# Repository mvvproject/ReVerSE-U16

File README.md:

# ReVerSE-U16
Development Kit

Плата ReVerSE-U16 ориентированна на создание SoC систем на микросхеме программируемой логики ПЛИС. Отлично подходит для домашнего обучения и позволяет полностью воссоздать множество ретро-компьютеров.
Для программирования используются программаторы и отладочные среды, позволяющие задать желаемую структуру цифрового устройства в виде принципиальной электрической схемы или программы на специальных языках описания аппаратуры: Verilog, VHDL, AHDL и др. В конфигурации ПЛИС реализуются почти все компоненты компьютера. Вне ПЛИС находятся только оперативная память, аппаратные интерфейсы для подключения клавиатуры, мыши, монитора, и других устройств.

#### Спецификация:
- FPGA Cyclone IV EP4CE22E22C8N (supports Cyclone III EP3C5/10/16/25, Cyclone IV EP4CE6/10/15/22)
- SDRAM 16MB x 16 bit (supports 4/16/32MB x 16 bit)
- SPI FLASH 64Mb (supports 64/16/1Mb)
- RTC DS1338Z + CR2032
- HDMI for sound and video (DVI or HDMI Male to VGA HD-15 15Pin Male Adapter Cable Cord)
- 10/100 Base-T Ethernet interface controller ENC424J600 with integrated MAC & PHY
- Dual USB 2.0 Host / Slave controller VNC2 (2 x ports)
- micro SD
- JTAG
- GPIO (uBUS)
- Power +5В 1A
- PCB Size 70 х 56 mm

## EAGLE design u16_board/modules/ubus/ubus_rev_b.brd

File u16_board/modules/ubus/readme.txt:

ReVerSE-U16 Adapter uBUS

09.06.2015	Rev.A Первая версия
16.09.2015	Rev.B Добавлены светодиоды LED1-8
05.10.2015	Rev.C Добавлена поддержка слотов расширения ZX-Bus, Nemo-Bus, NES, MSX-Bus

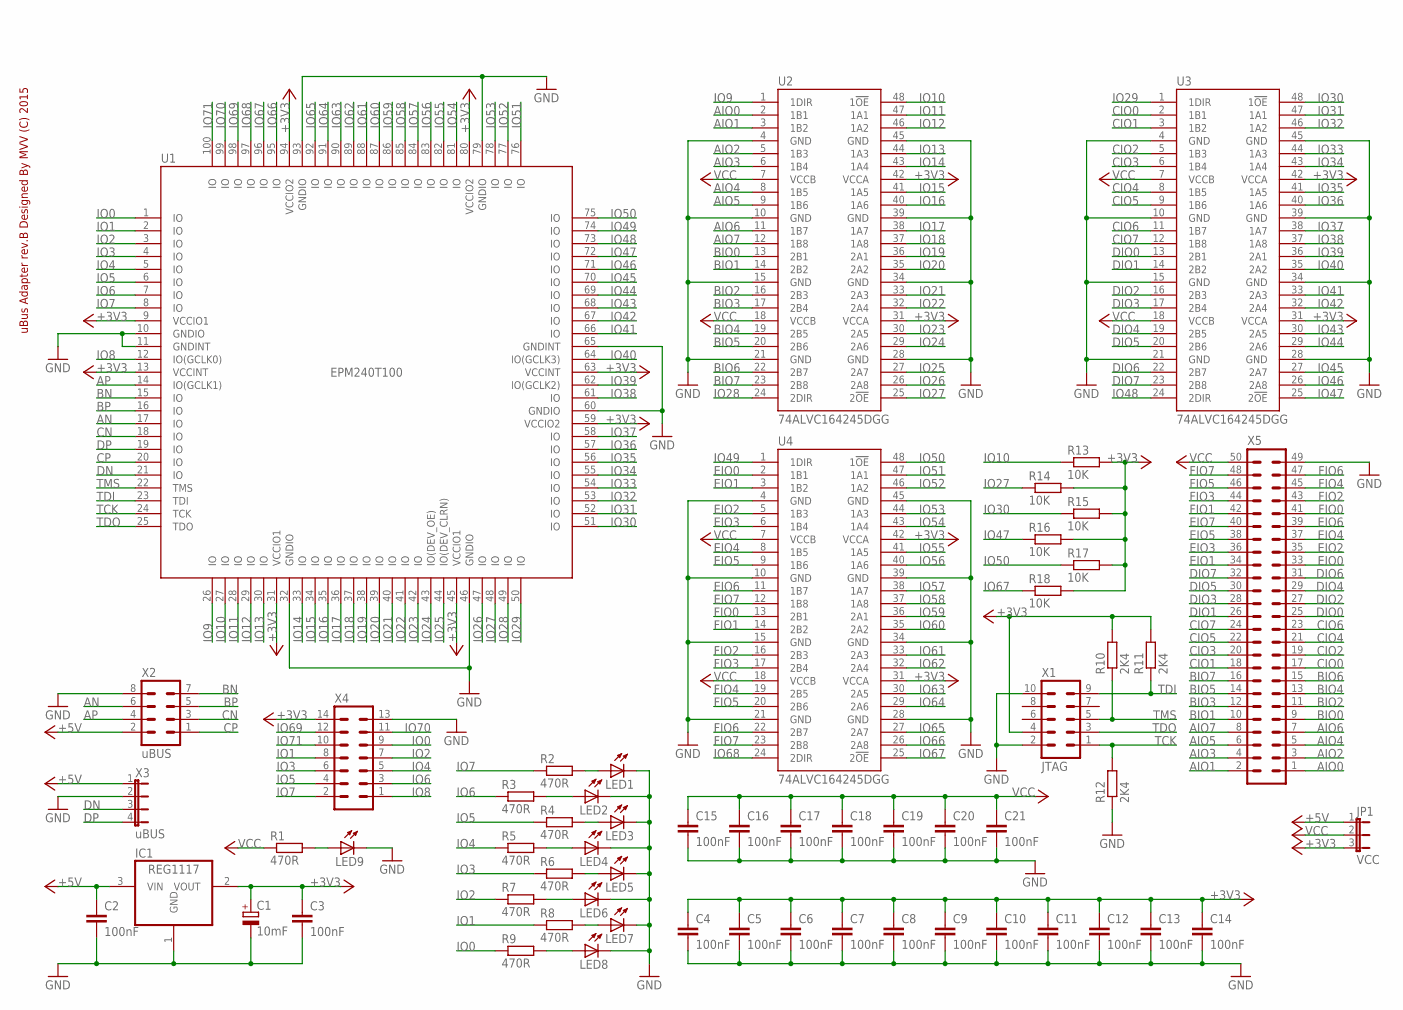
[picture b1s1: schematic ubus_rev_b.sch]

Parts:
C1: 10mF; CT6032
C2, C3, C4, C5, C6, C7, C8, C9, C10, C11, C12, C13, C14, C15, C16, C17, C18, C19, C20, C21: 100nF; C0805
IC1: REG1117; SOT223
JP1: VCC; JP2
LED1, LED2, LED3, LED4, LED5, LED6, LED7, LED8, LED9: LEDCHIPLED_0805; CHIPLED_0805
R1, R2, R3, R4, R5, R6, R7, R8, R9: 470R; R0805
R10, R11, R12: 2K4; R0805
R13, R14, R15, R16, R17, R18: 10K; R0805
U1: EPM240T100; TQFP100
U2, U3, U4: 74ALVC164245DGG; TSSOP48DGG
X1: JTAG; ML10
X2: uBUS; MA04-2
X3: uBUS; JP4
X4: ML14
X5: ML50

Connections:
+3V3: C1.+, C3.1, C4.1, C5.1, C6.1, C7.1, C8.1, C9.1, C10.1, C11.1, C12.1, C13.1, C14.1, IC1.2 (VOUT), JP1.3, R10.2, R11.2, R13.2, R14.2, R15.2, R16.2, R17.2, R18.2, U1.9 (VCCIO1), U1.13 (VCCINT), U1.31 (VCCIO1), U1.45 (VCCIO1), U1.59 (VCCIO2), U1.63 (VCCINT), U1.80 (VCCIO2), U1.94 (VCCIO2), U2.31 (VCCA), U2.42 (VCCA), U3.31 (VCCA), U3.42 (VCCA), U4.31 (VCCA), U4.42 (VCCA), X1.4, X4.14
+5V: C2.1, IC1.3 (VIN), JP1.1, X2.2, X3.1
AIO0: U2.2 (1B1), X5.1
AIO1: U2.3 (1B2), X5.2
AIO2: U2.5 (1B3), X5.3
AIO3: U2.6 (1B4), X5.4
AIO4: U2.8 (1B5), X5.5
AIO5: U2.9 (1B6), X5.6
AIO6: U2.11 (1B7), X5.7
AIO7: U2.12 (1B8), X5.8
AN: U1.17 (IO), X2.6
AP: U1.14 (IO(GCLK1)), X2.4
BIO0: U2.13 (2B1), X5.9
BIO1: U2.14 (2B2), X5.10
BIO2: U2.16 (2B3), X5.11
BIO3: U2.17 (2B4), X5.12
BIO4: U2.19 (2B5), X5.13
BIO5: U2.20 (2B6), X5.14
BIO6: U2.22 (2B7), X5.15
BIO7: U2.23 (2B8), X5.16
BN: U1.15 (IO), X2.7
BP: U1.16 (IO), X2.5
CIO0: U3.2 (1B1), X5.17
CIO1: U3.3 (1B2), X5.18
CIO2: U3.5 (1B3), X5.19
CIO3: U3.6 (1B4), X5.20
CIO4: U3.8 (1B5), X5.21
CIO5: U3.9 (1B6), X5.22
CIO6: U3.11 (1B7), X5.23
CIO7: U3.12 (1B8), X5.24
CN: U1.18 (IO), X2.3
CP: U1.20 (IO), X2.1
DIO0: U3.13 (2B1), X5.25
DIO1: U3.14 (2B2), X5.26
DIO2: U3.16 (2B3), X5.27
DIO3: U3.17 (2B4), X5.28
DIO4: U3.19 (2B5), X5.29
DIO5: U3.20 (2B6), X5.30
DIO6: U3.22 (2B7), X5.31
DIO7: U3.23 (2B8), X5.32
DN: U1.21 (IO), X3.3
DP: U1.19 (IO), X3.4
EIO0: U4.2 (1B1), X5.33
EIO1: U4.3 (1B2), X5.34
EIO2: U4.5 (1B3), X5.35
EIO3: U4.6 (1B4), X5.36
EIO4: U4.8 (1B5), X5.37
EIO5: U4.9 (1B6), X5.38
EIO6: U4.11 (1B7), X5.39
EIO7: U4.12 (1B8), X5.40
FIO0: U4.13 (2B1), X5.41
FIO1: U4.14 (2B2), X5.42
FIO2: U4.16 (2B3), X5.43
FIO3: U4.17 (2B4), X5.44
FIO4: U4.19 (2B5), X5.45
FIO5: U4.20 (2B6), X5.46
FIO6: U4.22 (2B7), X5.47
FIO7: U4.23 (2B8), X5.48
GND: C1.-, C2.2, C3.2, C4.2, C5.2, C6.2, C7.2, C8.2, C9.2, C10.2, C11.2, C12.2, C13.2, C14.2, C15.2, C16.2, C17.2, C18.2, C19.2, C20.2, C21.2, IC1.1 (GND), LED1.C, LED2.C, LED3.C, LED4.C, LED5.C, LED6.C, LED7.C, LED8.C, LED9.C, R12.1, U1.10 (GNDIO), U1.11 (GNDINT), U1.32 (GNDIO), U1.46 (GNDIO), U1.60 (GNDIO), U1.65 (GNDINT), U1.79 (GNDIO), U1.93 (GNDIO), U2.4 (GND), U2.10 (GND), U2.15 (GND), U2.21 (GND), U2.28 (GND), U2.34 (GND), U2.39 (GND), U2.45 (GND), U3.4 (GND), U3.10 (GND), U3.15 (GND), U3.21 (GND), U3.28 (GND), U3.34 (GND), U3.39 (GND), U3.45 (GND), U4.4 (GND), U4.10 (GND), U4.15 (GND), U4.21 (GND), U4.28 (GND), U4.34 (GND), U4.39 (GND), U4.45 (GND), X1.2, X1.10, X2.8, X3.2, X4.13, X5.49
IO0: R9.1, U1.1 (IO), X4.9
IO1: R8.1, U1.2 (IO), X4.8
IO2: R7.1, U1.3 (IO), X4.7
IO3: R6.1, U1.4 (IO), X4.6
IO4: R5.1, U1.5 (IO), X4.5
IO5: R4.1, U1.6 (IO), X4.4
IO6: R3.1, U1.7 (IO), X4.3
IO7: R2.1, U1.8 (IO), X4.2
IO8: U1.12 (IO(GCLK0)), X4.1
IO9: U1.26 (IO), U2.1 (1DIR)
IO10: R13.1, U1.27 (IO), U2.48 (1!OE)
IO11: U1.28 (IO), U2.47 (1A1)
IO12: U1.29 (IO), U2.46 (1A2)
IO13: U1.30 (IO), U2.44 (1A3)
IO14: U1.33 (IO), U2.43 (1A4)
IO15: U1.34 (IO), U2.41 (1A5)
IO16: U1.35 (IO), U2.40 (1A6)
IO17: U1.36 (IO), U2.38 (1A7)
IO18: U1.37 (IO), U2.37 (1A8)
IO19: U1.38 (IO), U2.36 (2A1)
IO20: U1.39 (IO), U2.35 (2A2)
IO21: U1.40 (IO), U2.33 (2A3)
IO22: U1.41 (IO), U2.32 (2A4)
IO23: U1.42 (IO), U2.30 (2A5)
IO24: U1.43 (IO(DEV_OE)), U2.29 (2A6)
IO25: U1.44 (IO(DEV_CLRN)), U2.27 (2A7)
IO26: U1.47 (IO), U2.26 (2A8)
IO27: R14.1, U1.48 (IO), U2.25 (2!OE)
IO28: U1.49 (IO), U2.24 (2DIR)
IO29: U1.50 (IO), U3.1 (1DIR)
IO30: R15.1, U1.51 (IO), U3.48 (1!OE)
IO31: U1.52 (IO), U3.47 (1A1)
IO32: U1.53 (IO), U3.46 (1A2)
IO33: U1.54 (IO), U3.44 (1A3)
IO34: U1.55 (IO), U3.43 (1A4)
IO35: U1.56 (IO), U3.41 (1A5)
IO36: U1.57 (IO), U3.40 (1A6)
IO37: U1.58 (IO), U3.38 (1A7)
IO38: U1.61 (IO), U3.37 (1A8)
IO39: U1.62 (IO(GCLK2)), U3.36 (2A1)
IO40: U1.64 (IO(GCLK3)), U3.35 (2A2)
IO41: U1.66 (IO), U3.33 (2A3)
IO42: U1.67 (IO), U3.32 (2A4)
IO43: U1.68 (IO), U3.30 (2A5)
IO44: U1.69 (IO), U3.29 (2A6)
IO45: U1.70 (IO), U3.27 (2A7)
IO46: U1.71 (IO), U3.26 (2A8)
IO47: R16.1, U1.72 (IO), U3.25 (2!OE)
IO48: U1.73 (IO), U3.24 (2DIR)
IO49: U1.74 (IO), U4.1 (1DIR)
IO50: R17.1, U1.75 (IO), U4.48 (1!OE)
IO51: U1.76 (IO), U4.47 (1A1)
IO52: U1.77 (IO), U4.46 (1A2)
IO53: U1.78 (IO), U4.44 (1A3)
IO54: U1.81 (IO), U4.43 (1A4)
IO55: U1.82 (IO), U4.41 (1A5)
IO56: U1.83 (IO), U4.40 (1A6)
IO57: U1.84 (IO), U4.38 (1A7)
IO58: U1.85 (IO), U4.37 (1A8)
IO59: U1.86 (IO), U4.36 (2A1)
IO60: U1.87 (IO), U4.35 (2A2)
IO61: U1.88 (IO), U4.33 (2A3)
IO62: U1.89 (IO), U4.32 (2A4)
IO63: U1.90 (IO), U4.30 (2A5)
IO64: U1.91 (IO), U4.29 (2A6)
IO65: U1.92 (IO), U4.27 (2A7)
IO66: U1.95 (IO), U4.26 (2A8)
IO67: R18.1, U1.96 (IO), U4.25 (2!OE)
IO68: U1.97 (IO), U4.24 (2DIR)
IO69: U1.98 (IO), X4.12
IO70: U1.99 (IO), X4.11
IO71: U1.100 (IO), X4.10
unnamed: LED1.A, R2.2
unnamed: LED2.A, R3.2
unnamed: LED3.A, R4.2
unnamed: LED4.A, R5.2
unnamed: LED5.A, R6.2
unnamed: LED6.A, R7.2
unnamed: LED7.A, R8.2
unnamed: LED8.A, R9.2
unnamed: LED9.A, R1.2
TCK: R12.2, U1.24 (TCK), X1.1
TDI: R11.1, U1.23 (TDI), X1.9
TDO: U1.25 (TDO), X1.3
TMS: R10.1, U1.22 (TMS), X1.5
VCC: C15.1, C16.1, C17.1, C18.1, C19.1, C20.1, C21.1, JP1.2, R1.1, U2.7 (VCCB), U2.18 (VCCB), U3.7 (VCCB), U3.18 (VCCB), U4.7 (VCCB), U4.18 (VCCB), X5.50

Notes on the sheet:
uBus Adapter rev.B Designed By MVV (C) 2015

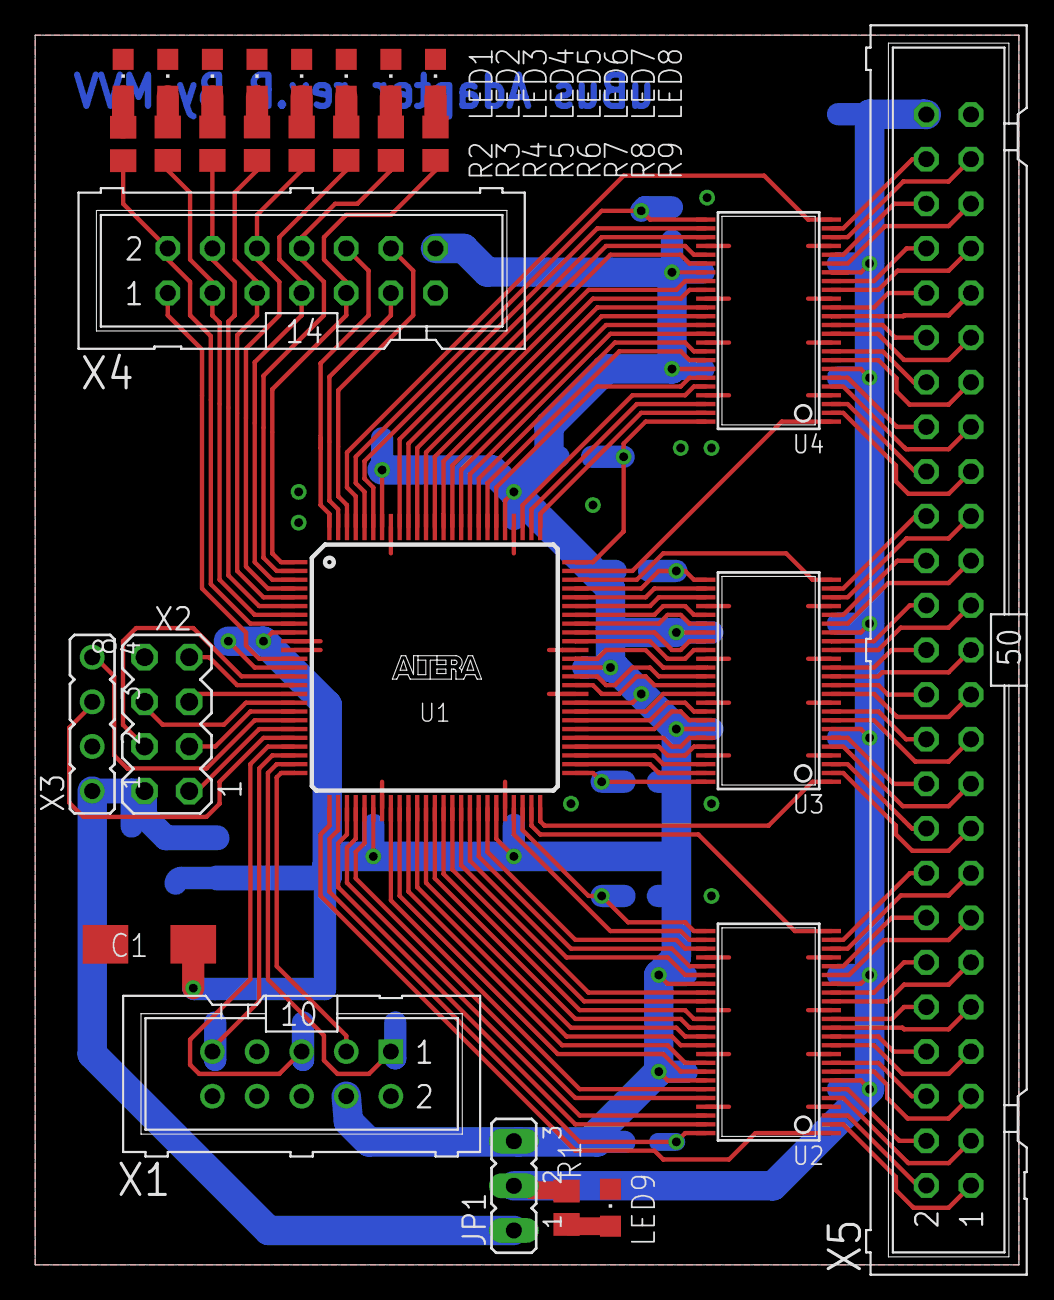
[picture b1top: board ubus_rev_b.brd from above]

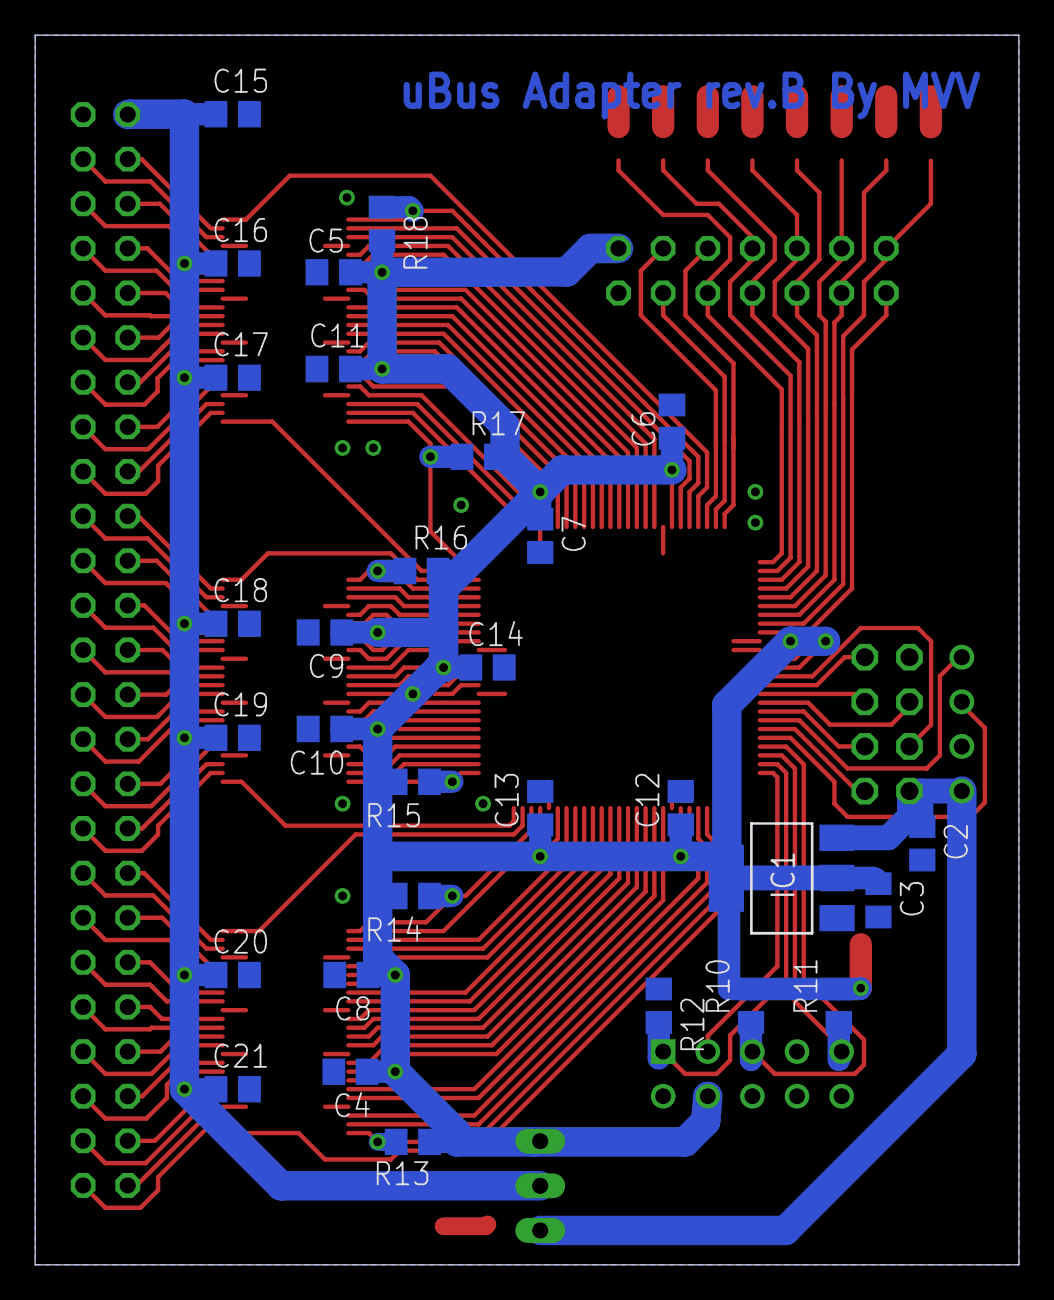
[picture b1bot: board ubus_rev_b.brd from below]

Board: 2 copper layers, 56.0 x 70.0 mm, 59 parts (30 on the bottom side), 145 nets.

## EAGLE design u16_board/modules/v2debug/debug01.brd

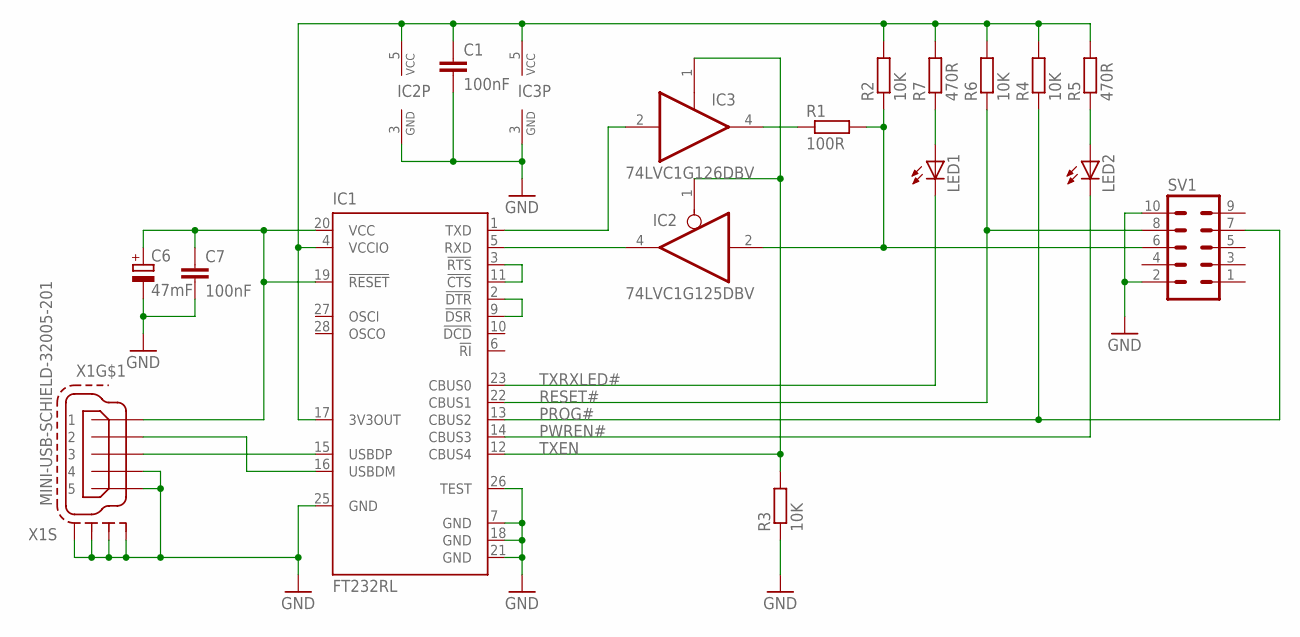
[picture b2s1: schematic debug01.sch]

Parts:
C1, C7: 100nF; C0603
C6: 47mF; CT3528
IC1: FT232RL; SSOP28
IC2: 74LVC1G125DBV; SOT23-5
IC3: 74LVC1G126DBV; SOT23-5
LED1, LED2: LEDCHIPLED_0805; CHIPLED_0805
R1: 100R; R0603
R2, R4, R6: 10K; R0603
R3: 10K; R1206
R5, R7: 470R; R0603
SV1: ML10
X1: MINI-USB-SCHIELD-32005-201; 32005-201

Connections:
+3V3: C1.1, IC1.4 (VCCIO), IC1.17 (3V3OUT), IC2.5 (VCC), IC3.5 (VCC), R2.2, R4.2, R5.2, R6.2, R7.2
+5V0: C6.+, C7.1, IC1.19 (!RESET), IC1.20 (VCC), X1.1
DBG: IC2.2 (I), R1.2, R2.1, SV1.6
DM: IC1.16 (USBDM), X1.2
DP: IC1.15 (USBDP), X1.3
GND: C1.2, C6.-, C7.2, IC1.7 (GND), IC1.18 (GND), IC1.21 (GND), IC1.25 (GND), IC1.26 (TEST), IC2.3 (GND), IC3.3 (GND), R3.1, SV1.2, SV1.10, X1.4, X1.5, X1.M1 (S1), X1.M2 (S2), X1.M3 (S3), X1.M4 (S4)
unnamed: LED2.A, R5.1
unnamed: IC3.4 (O), R1.1
unnamed: LED1.A, R7.1
unnamed: IC1.2 (!DTR), IC1.9 (!DSR)
unnamed: IC1.3 (!RTS), IC1.11 (!CTS)
PROG#: IC1.13 (CBUS2), R4.1, SV1.7
PWREN#: IC1.14 (CBUS3), LED2.C
RESET#: IC1.22 (CBUS1), R6.1, SV1.8
RXD: IC1.5 (RXD), IC2.4 (O)
TXD: IC1.1 (TXD), IC3.2 (I)
TXEN: IC1.12 (CBUS4), IC2.1 (OE), IC3.1 (OE), R3.2
TXRXLED#: IC1.23 (CBUS0), LED1.C

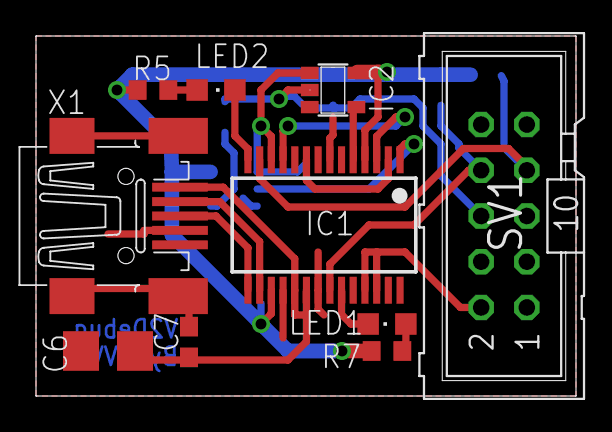
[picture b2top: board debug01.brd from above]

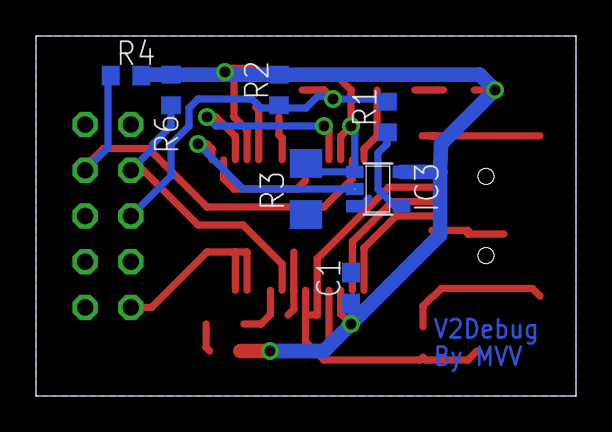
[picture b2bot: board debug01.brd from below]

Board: 2 copper layers, 30.0 x 20.0 mm, 17 parts (7 on the bottom side), 18 nets.

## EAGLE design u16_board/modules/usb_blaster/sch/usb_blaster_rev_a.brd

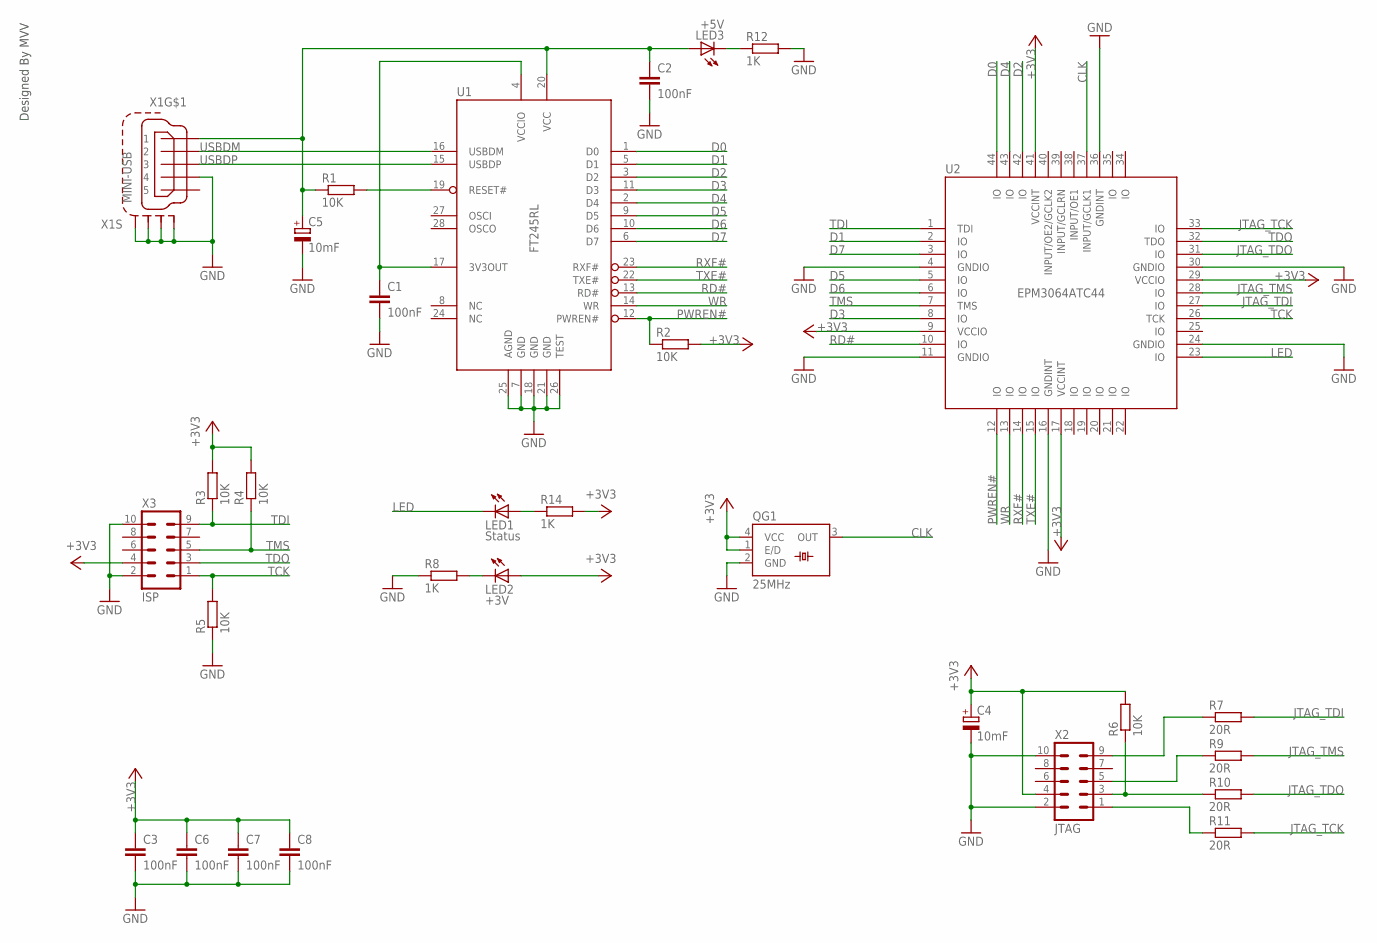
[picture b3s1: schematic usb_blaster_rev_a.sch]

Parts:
C1, C2, C3, C6, C7, C8: 100nF; C0805
C4, C5: 10mF; CT6032
LED1: Status; LED3MM
LED2: +3V; LED3MM
LED3: +5V; LED3MM
QG1: 25MHz; SM77H
R1, R2, R3, R4, R5, R6: 10K; R0805
R7, R9, R10, R11: 20R; R0805
R8, R12, R14: 1K; R0805
U1: FT245RL; SSOP28
U2: EPM3064ATC44; TQFP44
X1: MINI-USB; 32005-201
X2: JTAG; ML10
X3: ISP; MA05-2

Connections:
3V3OUT: C1.1, U1.4 (VCCIO), U1.17 (3V3OUT)
+3V3: C3.1, C4.+, C6.1, C7.1, C8.1, LED2.A, QG1.1 (E/D), QG1.4 (VCC), R2.2, R3.2, R4.2, R6.2, R14.2, U2.9 (VCCIO), U2.17 (VCCINT), U2.29 (VCCIO), U2.41 (VCCINT), X2.4, X3.4
+5V: C2.1, C5.+, LED3.A, R1.1, U1.20 (VCC), X1.1
CLK: QG1.3 (OUT), U2.37 (INPUT/GCLK1)
D0: U1.1 (D0), U2.44 (IO)
D1: U1.5 (D1), U2.2 (IO)
D2: U1.3 (D2), U2.42 (IO)
D3: U1.11 (D3), U2.8 (IO)
D4: U1.2 (D4), U2.43 (IO)
D5: U1.9 (D5), U2.5 (IO)
D6: U1.10 (D6), U2.6 (IO)
D7: U1.6 (D7), U2.3 (IO)
GND: C1.2, C2.2, C3.2, C4.-, C5.-, C6.2, C7.2, C8.2, QG1.2 (GND), R5.1, R8.1, R12.2, U1.7 (GND), U1.18 (GND), U1.21 (GND), U1.25 (AGND), U1.26 (TEST), U2.4 (GNDIO), U2.11 (GNDIO), U2.16 (GNDINT), U2.24 (GNDIO), U2.30 (GNDIO), U2.36 (GNDINT), X1.4, X1.M1 (S1), X1.M2 (S2), X1.M3 (S3), X1.M4 (S4), X2.2, X2.10, X3.2, X3.10
JTAG_TCK: R11.2, U2.33 (IO)
JTAG_TDI: R7.2, U2.27 (IO)
JTAG_TDO: R10.2, U2.31 (IO)
JTAG_TMS: R9.2, U2.28 (IO)
LED: LED1.K (C), U2.23 (IO)
unnamed: LED3.K (C), R12.1
unnamed: R1.2, U1.19 (RESET#)
unnamed: R7.1, X2.9
unnamed: R11.1, X2.1
unnamed: R6.1, R10.1, X2.3
unnamed: R9.1, X2.5
unnamed: LED2.K (C), R8.2
unnamed: LED1.A, R14.1
PWREN#: R2.1, U1.12 (PWREN#), U2.12 (IO)
RD#: U1.13 (RD#), U2.10 (IO)
RXF#: U1.23 (RXF#), U2.14 (IO)
TCK: R5.2, U2.26 (TCK), X3.1
TDI: R3.1, U2.1 (TDI), X3.9
TDO: U2.32 (TDO), X3.3
TMS: R4.1, U2.7 (TMS), X3.5
TXE#: U1.22 (TXE#), U2.15 (IO)
USBDM: U1.16 (USBDM), X1.2
USBDP: U1.15 (USBDP), X1.3
WR: U1.14 (WR), U2.13 (IO)

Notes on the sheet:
Designed By MVV

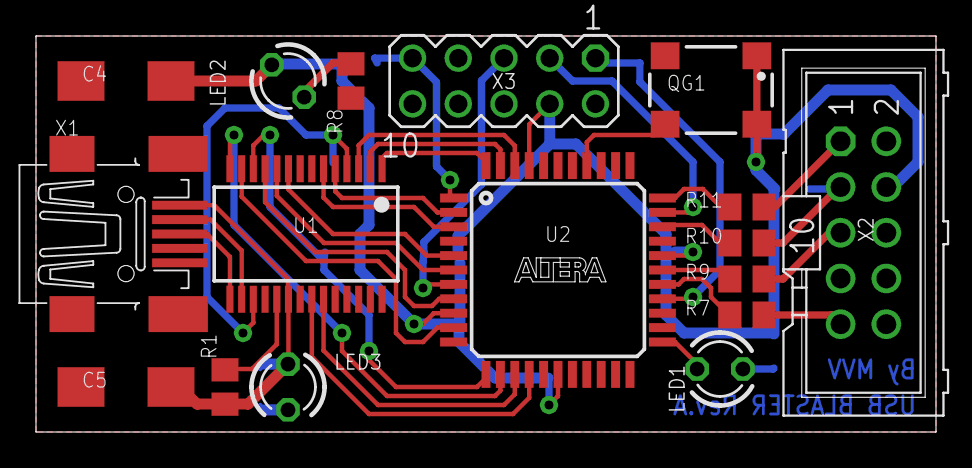
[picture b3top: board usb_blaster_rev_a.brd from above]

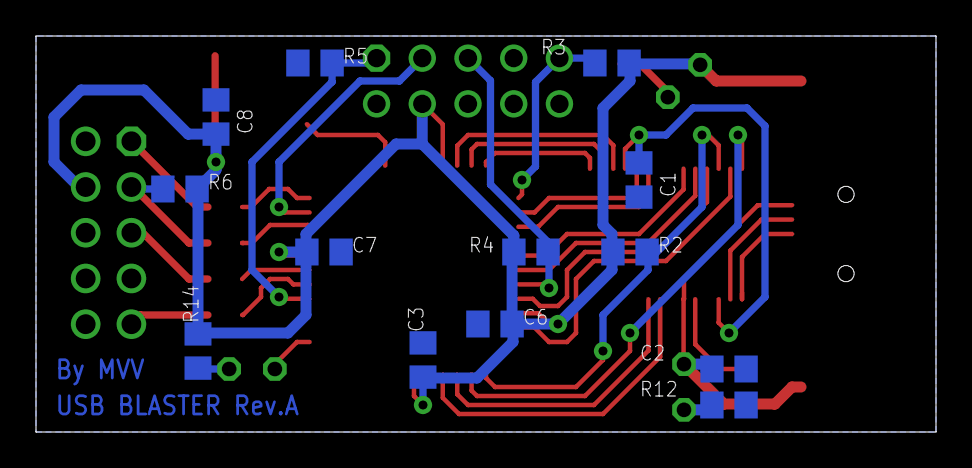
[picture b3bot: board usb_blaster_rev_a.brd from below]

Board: 2 copper layers, 50.0 x 22.0 mm, 30 parts (13 on the bottom side), 37 nets.
